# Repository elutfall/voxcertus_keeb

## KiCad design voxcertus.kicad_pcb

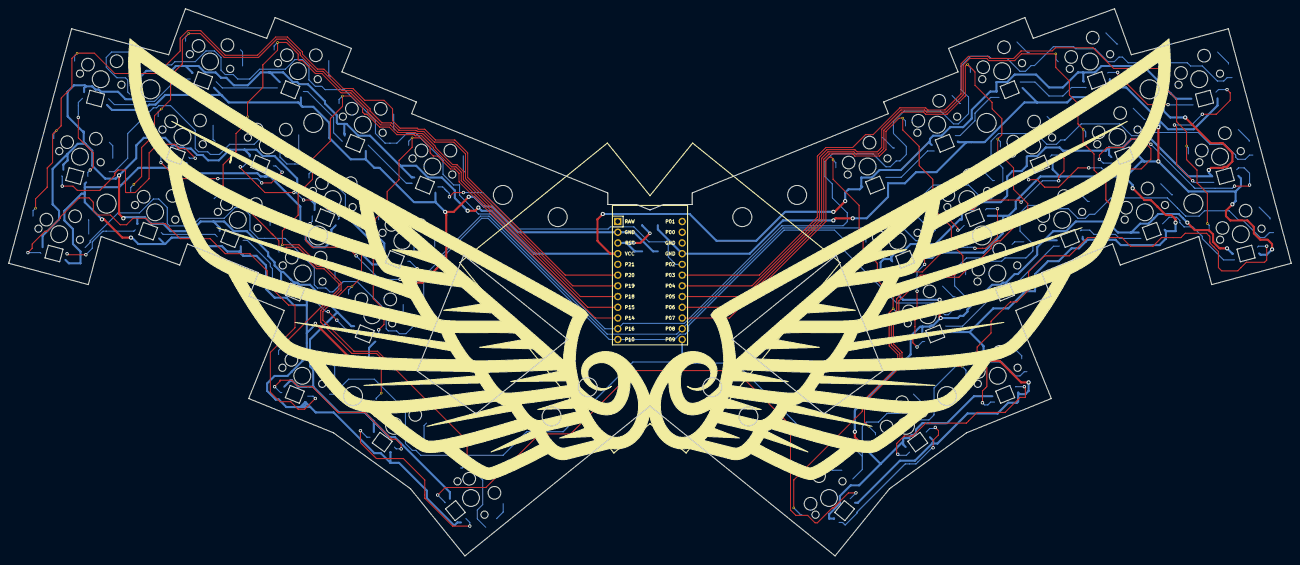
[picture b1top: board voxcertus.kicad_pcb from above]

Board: 2 copper layers, 303.7 x 129.6 mm, 146 parts (0 on the bottom side), 54 nets.

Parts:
B1: SW_TACT_ALPS_SKQGABE010
D1, D2, D3, D4, D5, D6, D7, D8, D9, D10, D11, D12, D13, D14, D15, D16, D17, D18, D19, D20, D21, D22, D23, D24, D25, D26, D27, D28, D29, D30, D31, D32, D33, D34, D35, D36: ComboDiode
LED1, LED2, LED3, LED4, LED5, LED6, LED7, LED8, LED9, LED10, LED11, LED12, LED13, LED14, LED15, LED16, LED17, LED18, LED19, LED20, LED21, LED22, LED23, LED24, LED25, LED26, LED27, LED28, LED29, LED30, LED31, LED32, LED33, LED34, LED35, LED36: WS2812B
MCU1: ProMicro
S1, S2, S3, S4, S5, S6, S7, S8, S9, S10, S11, S12, S13, S14, S15, S16, S17, S18, S19, S20, S21, S22, S23, S24, S25, S26, S27, S28, S29, S30, S31, S32, S33, S34, S35, S36: MX
SW6, SW6#2, SW6#3, SW6#4, SW6#5, SW6#6, SW6#7, SW6#8, SW6#9, SW6#10, SW6#11, SW6#12, SW6#13, SW6#14, SW6#15, SW6#16, SW6#17, SW6#18, SW6#19, SW6#20, SW6#21, SW6#22, SW6#23, SW6#24, SW6#25, SW6#26, SW6#27, SW6#28, SW6#29, SW6#30, SW6#31, SW6#32, SW6#33, SW6#34, SW6#35, SW6#36: SW_PUSH; CherryMX_Hotswap

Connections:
GND: B1.2, LED1.3, LED2.3, LED3.3, LED4.3, LED5.3, LED6.3, LED7.3, LED8.3, LED9.3, LED10.3, LED11.3, LED12.3, LED13.3, LED14.3, LED15.3, LED16.3, LED17.3, LED18.3, LED19.3, LED20.3, LED21.3, LED22.3, LED23.3, LED24.3, LED25.3, LED26.3, LED27.3, LED28.3, LED29.3, LED30.3, LED31.3, LED32.3, LED33.3, LED34.3, LED35.3, LED36.3, MCU1.2, MCU1.15, MCU1.16
P2: LED1.2, LED1.4, LED2.2, LED2.4, LED3.2, LED3.4, LED4.2, LED4.4, LED5.2, LED5.4, LED6.2, LED6.4, LED7.2, LED7.4, LED8.2, LED8.4, LED9.2, LED9.4, LED10.2, LED10.4, LED11.2, LED11.4, LED12.2, LED12.4, LED13.2, LED13.4, LED14.2, LED14.4, LED15.2, LED15.4, LED16.2, LED16.4, LED17.2, LED17.4, LED18.2, LED18.4, LED19.2, LED19.4, LED20.2, LED20.4, LED21.2, LED21.4, LED22.2, LED22.4, LED23.2, LED23.4, LED24.2, LED24.4, LED25.2, LED25.4, LED26.2, LED26.4, LED27.2, LED27.4, LED28.2, LED28.4, LED29.2, LED29.4, LED30.2, LED30.4, LED31.2, LED31.4, LED32.2, LED32.4, LED33.2, LED33.4, LED34.2, LED34.4, LED35.2, LED35.4, LED36.2, LED36.4, MCU1.17
P3: MCU1.18, S19.1, S20.1, S21.1
P4: MCU1.19, S22.1, S23.1, S24.1
P5: MCU1.20, S25.1, S26.1, S27.1, S34.1
P6: MCU1.21, S28.1, S29.1, S30.1, S35.1
P7: MCU1.22, S31.1, S32.1, S33.1, S36.1
P8: D2.1, D5.1, D8.1, D11.1, D14.1, D20.1, D23.1, D26.1, D29.1, D32.1, MCU1.23
P9: D16.1, D17.1, D18.1, D34.1, D35.1, D36.1, MCU1.24
P10: D1.1, D4.1, D7.1, D10.1, D13.1, D19.1, D22.1, D25.1, D28.1, D31.1, MCU1.12
P14: MCU1.10, S13.1, S14.1, S15.1, S18.1
P15: MCU1.9, S10.1, S11.1, S12.1, S17.1
P16: D3.1, D6.1, D9.1, D12.1, D15.1, D21.1, D24.1, D27.1, D30.1, D33.1, MCU1.11
P18: MCU1.8, S7.1, S8.1, S9.1, S16.1
P19: MCU1.7, S4.1, S5.1, S6.1
P20: MCU1.6, S1.1, S2.1, S3.1
RST: B1.1, MCU1.3
VCC: LED1.1, LED2.1, LED3.1, LED4.1, LED5.1, LED6.1, LED7.1, LED8.1, LED9.1, LED10.1, LED11.1, LED12.1, LED13.1, LED14.1, LED15.1, LED16.1, LED17.1, LED18.1, LED19.1, LED20.1, LED21.1, LED22.1, LED23.1, LED24.1, LED25.1, LED26.1, LED27.1, LED28.1, LED29.1, LED30.1, LED31.1, LED32.1, LED33.1, LED34.1, LED35.1, LED36.1, MCU1.4
far_thumb: D18.2, S18.2
home_thumb: D17.2, S17.2
index_bottom: D10.2, S10.2
index_home: D11.2, S11.2
index_top: D12.2, S12.2
inner_bottom: D13.2, S13.2
inner_home: D14.2, S14.2
inner_top: D15.2, S15.2
middle_bottom: D7.2, S7.2
middle_home: D8.2, S8.2
middle_top: D9.2, S9.2
mirror_far_thumb: D36.2, S36.2
mirror_home_thumb: D35.2, S35.2
mirror_index_bottom: D28.2, S28.2
mirror_index_home: D29.2, S29.2
mirror_index_top: D30.2, S30.2
mirror_inner_bottom: D31.2, S31.2
mirror_inner_home: D32.2, S32.2
mirror_inner_top: D33.2, S33.2
mirror_middle_bottom: D25.2, S25.2
mirror_middle_home: D26.2, S26.2
mirror_middle_top: D27.2, S27.2
mirror_near_thumb: D34.2, S34.2
mirror_pinky_bottom: D19.2, S19.2
mirror_pinky_home: D20.2, S20.2
mirror_pinky_top: D21.2, S21.2
mirror_ring_bottom: D22.2, S22.2
mirror_ring_home: D23.2, S23.2
mirror_ring_top: D24.2, S24.2
near_thumb: D16.2, S16.2
pinky_bottom: D1.2, S1.2
pinky_home: D2.2, S2.2
pinky_top: D3.2, S3.2
ring_bottom: D4.2, S4.2
ring_home: D5.2, S5.2
ring_top: D6.2, S6.2

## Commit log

2022-10-05 first post
